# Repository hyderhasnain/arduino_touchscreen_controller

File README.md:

**Arduino Touchscreen LCD Wireless Controller Project** 
=========================================================

You can see this project in action here: http://www.youtube.com/watch?v=bEqvmakN07w

##Background

I designed and built this project during summer 2013, as an upgrade to a previous wireless controller I built the previous summer to control a small robot. That controller used an LED ring to display orientation and driving direction, communicating via XBee, but I needed a wireless controller with more functionality and input options.
So I found this LCD via Adafruit (https://www.adafruit.com/products/335). Perfect!

  >Turns out a newer version came out soon afterwards, that uses SPI instead of a parallel connection. Much fewer pins, easier to use, etc. Bummer, *lots* of my design decisions and compromises revolved around the limited IO on the Arduino... Oh well. 

I wanted the board to have many features, including: accelerometer control, wireless communication, wireless programming, real time clock, onboard battery charging, joysticks, microSD card, light sensor, advanced math computation, etc. Of course, this meant I had to design a custom PCB.

##Design

During this process, I made a number of Eagle library parts for many components, including the Adafruit LCD, microSD card breakout, ADXL345 accelerometer, MCP3008, uM-FPU chip, and Arduino Fio by transplanting designs from datasheets and PCB designs. I've included my library because I personally couldn't find these parts online, and maybe these will help somebody. I planned to design the entire schematic/board in Cadsoft Eagle, but after completing the schematic realized that the free version of Eagle limits the maximum size of the board, and my board wouldn't fit. After much frustration and fiddling, I decided to use DipTrace to layout the PCB. I exported my schematic and un-routed board from Eagle into DipTrace, and after managed to get all the parts showing up properly. The only huge problem was that I wouldn't be able to modify my circuit because the schematic was in Eagle and the PCB was in DipTrace. My first "real" PCB I designed, pretty good job I guess. Manufactured by OSHPark, great quality and price. 

##Code

###Graphing Program

Adafruit wrote awesome driver and graphics libraries for their LCDs, which you can find on the LCD product pages.
I wrote many programs for this board, the highlight of which is currently an accelerometer graphing program. Unfortunately, there isn't enough flash memory to use both the SD library and TouchScreen library. So you can't both log data *and* have on-screen controls. The program reads accelerometer data from the ADXL345, and displays it on the LCD via an interactive, color-coded interface. 
The graphing code works by storing two variables for each accelerometer axis(XYZ), a "old" value and "new" value. A line is drawn between the values, which are updated each time data is read. 
The code is heavily commented.
The code also contains snippets to enable drawing circles. Lots of other stuff is commented out, for example if you want to enable SD card logging, comment out the touchscreen code and un-comment the SD card code. Read Adafruit's writeup of their graphics library! :)

There are *two* versions of the code, one without any input from the MCP3008 (joysticks, voltage sensor, light sensor) and one with. The one without is faster.

This code probably contains lots of stuff that I need specifically for this board, but you can probably figure it out.

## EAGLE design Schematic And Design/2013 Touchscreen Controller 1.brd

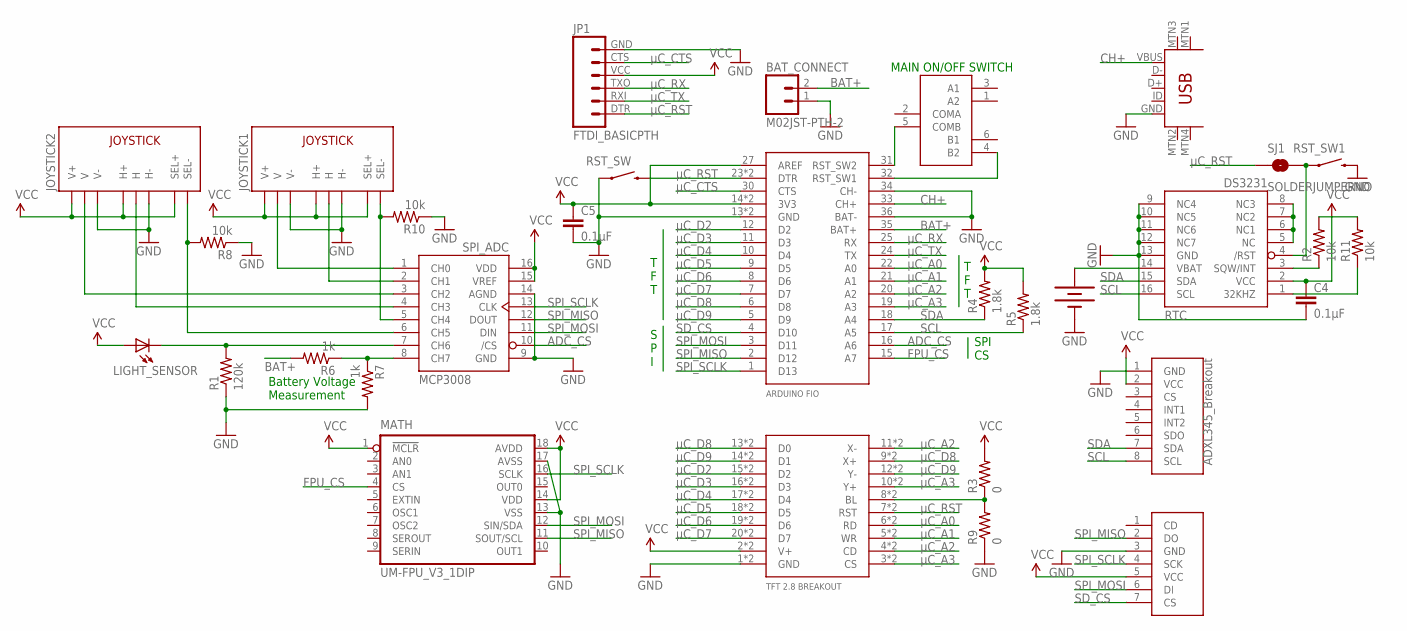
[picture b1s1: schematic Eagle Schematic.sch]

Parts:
ACCEL1: ADXL345_BREAKOUT; 1X08
BAT1: BATTERY12MM; BATTCON_12MM
BAT_CONNECT: M02JST-PTH-2; JST-2-PTH
C4, C5: 0.1µF; CAP-PTH-SMALL
JOYSTICK1, JOYSTICK2: JOYSTICKPTH; JOYSTICK
JP1: FTDI_BASICPTH; FTDI_BASIC
LIGHT_SENSOR: LED5MM
MATH: UM-FPU_V3_1DIP; DIL18
R1: 120k; AXIAL-0.4
R2, R8, R10, R11: 10k; AXIAL-0.4
R3, R9: 0; AXIAL-0.4
R4, R5: 1.8k; AXIAL-0.4
R6, R7: 1k; AXIAL-0.4
RST_SW, RST_SW1: SWITCH-MOMENTARY-2PTH; TACTILE-PTH
RTC: DS3231/SO; SO16W
SJ1: SOLDERJUMPERNO; SJ_2S-NO
SPI_ADC: MCP3008; DIL16
U$1: ARDUINOFIO
U$2: TFT2.8BREAKOUT
U$3: RIGHTANGLE_DPDT_PTH
U$4: MICROSD_BREAKOUT
USB_CHARGE: USB-MINIB-5PIN; USB-MINIB

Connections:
ADC_CS: SPI_ADC.10 (/CS), U$1.16 (A6)
BAT+: BAT_CONNECT.2, R6.P$2 (2), U$1.35 (BAT+)
CH+: U$1.33 (CH+), USB_CHARGE.VBUS
FPU_CS: MATH.4 (CS), U$1.15 (A7)
GND: ACCEL1.1 (GND), BAT1.GND (-), BAT_CONNECT.1, C4.2, C5.2, JOYSTICK1.H3 (H-), JOYSTICK1.V3 (V-), JOYSTICK2.H3 (H-), JOYSTICK2.V3 (V-), JP1.GND (6), MATH.13 (VSS), MATH.17 (AVSS), R1.P$1 (1), R7.P$2 (2), R8.P$1 (1), R9.P$1 (1), R10.P$1 (1), RST_SW.1, RST_SW1.3 (2), RTC.9 (NC4), RTC.10 (NC5), RTC.11 (NC6), RTC.12 (NC7), RTC.13 (GND), SPI_ADC.9 (GND), SPI_ADC.14 (AGND), U$1.13 (GND), U$1.28 (GND), U$1.34 (CH-), U$1.36 (BAT-), U$2.1 (GND), U$2.21 (GND), U$4.3 (GND), USB_CHARGE.GND
unnamed: JOYSTICK1.B2A (SEL-), R10.P$2 (2), SPI_ADC.5 (CH4)
unnamed: JOYSTICK2.B2A (SEL-), R8.P$2 (2), SPI_ADC.6 (CH5)
unnamed: LIGHT_SENSOR.K (C), R1.P$2 (2), SPI_ADC.7 (CH6)
unnamed: U$1.31 (RST_SW2), U$3.5 (COMB)
unnamed: U$1.32 (RST_SW1), U$3.4 (B2)
unnamed: RST_SW1.1, RTC.4 (/RST), SJ1.2
unnamed: R3.P$1 (1), R9.P$2 (2), U$2.8 (BL), U$2.34 (BL)
unnamed: R6.P$1 (1), R7.P$1 (1), SPI_ADC.8 (CH7)
unnamed: BAT1.PWR@1 (+), RTC.14 (VBAT)
unnamed: R2.P$1 (1), RTC.3 (SQW/INT)
unnamed: R11.P$1 (1), RTC.1 (32KHZ)
unnamed: R2.P$2 (2), R11.P$2 (2)
unnamed: JOYSTICK1.V2 (V), SPI_ADC.1 (CH0)
unnamed: JOYSTICK1.H2 (H), SPI_ADC.2 (CH1)
unnamed: JOYSTICK2.V2 (V), SPI_ADC.3 (CH2)
unnamed: JOYSTICK2.H2 (H), SPI_ADC.4 (CH3)
unnamed: RTC.5 (NC), RTC.6 (NC1), RTC.7 (NC2), RTC.8 (NC3)
SCL: ACCEL1.8 (SCL), R5.P$1 (1), RTC.16 (SCL), U$1.17 (A5)
SDA: ACCEL1.7 (SDA), R4.P$1 (1), RTC.15 (SDA), U$1.18 (A4)
SD_CS: U$1.4 (D10), U$4.7 (CS)
SPI_MISO: MATH.11 (SOUT/SCL), SPI_ADC.12 (DOUT), U$1.2 (D12), U$4.2 (DO)
SPI_MOSI: MATH.12 (SIN/SDA), SPI_ADC.11 (DIN), U$1.3 (D11), U$4.6 (DI)
SPI_SCLK: MATH.16 (SCLK), SPI_ADC.13 (CLK), U$1.1 (D13), U$4.4 (SCK)
VCC: ACCEL1.2 (VCC), C4.1, C5.1, JOYSTICK1.B1A (SEL+), JOYSTICK1.H1 (H+), JOYSTICK1.V1 (V+), JOYSTICK2.B1A (SEL+), JOYSTICK2.H1 (H+), JOYSTICK2.V1 (V+), JP1.VCC (4), LIGHT_SENSOR.A, MATH.1 (!MCLR), MATH.14 (VDD), MATH.18 (AVDD), R3.P$2 (2), R4.P$2 (2), R5.P$2 (2), RTC.2 (VCC), SPI_ADC.15 (VREF), SPI_ADC.16 (VDD), U$1.14 (3V3), U$1.26 (3V3), U$1.27 (AREF), U$2.2 (V+), U$2.31 (V+), U$4.5 (VCC)
µC_A0: U$1.22 (A0), U$2.6 (RD), U$2.33 (RD)
µC_A1: U$1.21 (A1), U$2.5 (WR), U$2.23 (WR)
µC_A2: U$1.20 (A2), U$2.4 (CD), U$2.11 (X-), U$2.26 (X-), U$2.32 (CD)
µC_A3: U$1.19 (A3), U$2.3 (CS), U$2.10 (Y+), U$2.22 (CS), U$2.35 (Y+)
µC_CTS: JP1.CTS (5), U$1.30 (CTS)
µC_D2: U$1.12 (D2), U$2.15 (D2), U$2.28 (D2)
µC_D3: U$1.11 (D3), U$2.16 (D3), U$2.38 (D3)
µC_D4: U$1.10 (D4), U$2.17 (D4), U$2.29 (D4)
µC_D5: U$1.9 (D5), U$2.18 (D5), U$2.39 (D5)
µC_D6: U$1.8 (D6), U$2.19 (D6), U$2.30 (D6)
µC_D7: U$1.7 (D7), U$2.20 (D7), U$2.40 (D7)
µC_D8: U$1.6 (D8), U$2.9 (X+), U$2.13 (D0), U$2.25 (X+), U$2.27 (D0)
µC_D9: U$1.5 (D9), U$2.12 (Y-), U$2.14 (D1), U$2.36 (Y-), U$2.37 (D1)
µC_RST: JP1.DTR (1), RST_SW.3 (2), SJ1.1, U$1.23 (DTR), U$1.29 (DTR), U$2.7 (RST), U$2.24 (RST)
µC_RX: JP1.TXO (3), U$1.25 (RX)
µC_TX: JP1.RXI (2), U$1.24 (TX)

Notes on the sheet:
T F T
S P I
SPI CS
Battery Voltage Measurement
MAIN ON/OFF SWITCH

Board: 2 copper layers, 31 parts (0 on the bottom side), 45 nets, no tracks yet.

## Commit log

2014-02-12 Initial Commit of Original Graphing Code
    Original touchscreen graphing and SD logging code. Contains lots of
    code, some is commented out.
2014-02-12 Remove unnecessary EasyTransfer code
2014-02-12 Initial Commit of Graphing Code
2014-02-12 Cleanup
2014-02-12 Removed redundant variables
2014-02-12 Comments
2014-02-13 Added links
2014-02-13 Added Eagle and Diptrace files
    Note: Eagle BRD file isn't routed at all. I routed the board in Diptrace
2014-02-13 Added Eagle and Diptrace schematic/pcb files
    Note: Eagle PCB file not routed, wasn't used other than to export into
    Diptrace.

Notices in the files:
parts and their libraries:
SparkFun-Electromechanical: Licensing: CC v3.0 Share-Alike You are welcome to use this library for commercial purposes.
